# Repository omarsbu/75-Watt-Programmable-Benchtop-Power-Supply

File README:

In progress...
  => Finish Fusion 360 schematic & PCB layout
  => Finish Microcontroller Software

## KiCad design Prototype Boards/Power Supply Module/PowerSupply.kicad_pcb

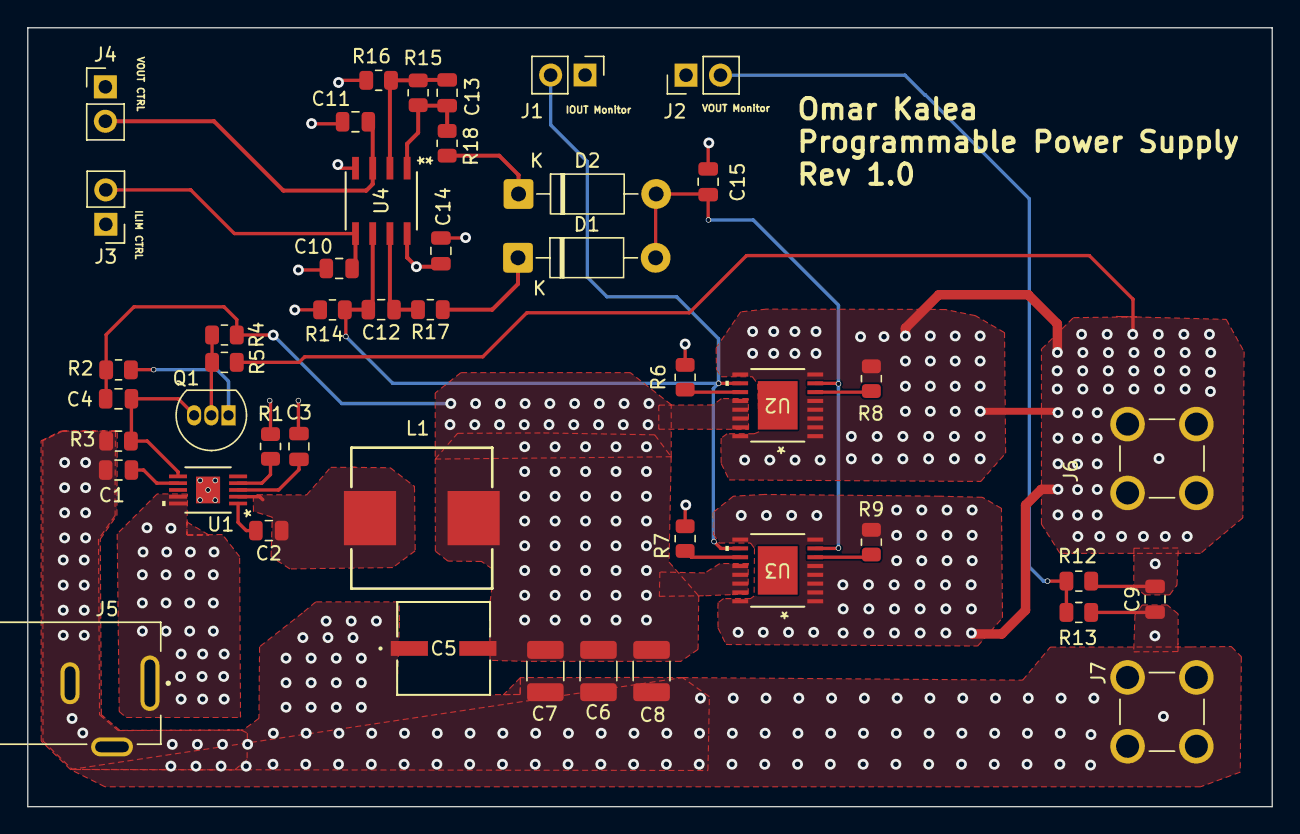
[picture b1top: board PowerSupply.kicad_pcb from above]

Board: 4 copper layers, 91.9 x 57.5 mm, 46 parts (0 on the bottom side), 26 nets.

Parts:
C1, C2, C10, C11, C14, C15: 0.1u; C_0805_2012Metric
C3: 1u; C_0805_2012Metric
C4, C12: 1n; C_0805_2012Metric
C5: 100u; CHEMI-F80-L
C6, C7, C8: 33u; C_1210_3225Metric_Pad1.33x2.70mm_HandSolder
C9: 10u; C_0805_2012Metric
C13: 100p; C_0805_2012Metric
D1, D2: 1N5819; D_DO-41_SOD81_P10.16mm_Horizontal
J1, J2, J3, J4: PinHeader_1x02_P2.54mm_Vertical
J5: 54-00130; TENSILITY_54-00130
J6: CT3151-2; CALTEST_CT3151-0
J7: CT3151-0; CALTEST_CT3151-0
L1: 2.2uH; WE-HCI_1050
Q1: 2N3906; TO-92_Inline
R1: 20k; R_0805_2012Metric
R2, R6, R7, R13, R16: 1k; R_0805_2012Metric
R3: 4k; R_0805_2012Metric
R4, R5: 100k; R_0805_2012Metric
R8, R9: 10k; R_0805_2012Metric
R12, R15: 9k; R_0805_2012Metric
R14: 5k; R_0805_2012Metric
R17, R18: 10; R_0805_2012Metric
U1: LT8609HMSE-TRPBF; 05-08-1664_ADI
U2, U3: LT3081HFE-PBF; TSSOP-16_FE&slash_BB_LIT-L
U4: ADA4091-2ARZ-R7; R_8_ADI-L

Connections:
+24V: C14.2, J5.A, U1.9 (VIN), U1.10 (EN/UV), U4.8 (V+)
/Power Stage/IMON: C12.2, J1.2, R14.1, U2.10 (IMON), U3.10 (IMON), U4.6 (INB-)
/Power Stage/LDO_IN: C4.1, C5.2, C6.2, C7.2, C8.2, L1.2, R2.2, R4.1, U2.12 (IN), U2.13 (IN), U2.14 (IN), U2.15 (IN), U3.12 (IN), U3.13 (IN), U3.14 (IN), U3.15 (IN)
/Power Stage/SW: C2.1, L1.1, U1.2 (SW)
/Power Stage/VMON: J2.2, R12.1, R13.2
/Power Stage/VSET: C15.1, D1.2 (A), D2.2 (A), U2.7 (SET), U3.7 (SET)
/Setpoint Control/CC_SET: C10.1, J3.2, U4.5 (INB+)
/Setpoint Control/CV_SET: C11.1, J4.2, U4.3 (INA+)
GND: C1.2, C3.1, C5.1, C6.1, C7.1, C8.1, C9.1, C10.2, C11.2, C14.1, C15.2, J1.1, J2.1, J3.1, J4.1, J5.B, J5.C, J7.1, J7.2 (1), J7.3 (1), J7.4 (1), R1.1, R3.1, R6.1, R7.1, R13.1, R14.2, R16.2, U1.11 (GND), U2.17 (EPAD), U3.17 (EPAD), U4.4 (V-)
unnamed: D1.1 (K), R17.1
unnamed: D2.1 (K), R18.1
unnamed: Q1.2 (B), R4.2, R5.1
unnamed: C4.2, Q1.3 (C), R3.2, U1.6 (FB)
unnamed: Q1.1 (E), R2.1
unnamed: C2.2, U1.1 (BST)
unnamed: C3.2, U1.3 (INTVCC)
unnamed: R1.2, U1.4 (RT)
unnamed: C1.1, U1.7 (TR/SS)
unnamed: R8.2, U2.6 (ILIM)
unnamed: R6.2, U2.11 (TEMP)
unnamed: R9.1, U3.6 (ILIM)
unnamed: R7.2, U3.11 (TEMP)
unnamed: C13.2, R15.2, R16.1, U4.2 (INA-)
unnamed: C13.1, R15.1, R18.2, U4.1 (OUTA)
unnamed: C12.1, R17.2, U4.7 (OUTB)
VOUT: C9.2, J6.1, J6.2 (1), J6.3 (1), J6.4 (1), R5.2, R8.1, R9.2, R12.2, U2.1 (OUT), U2.2 (OUT), U2.3 (OUT), U2.4 (OUT), U2.5 (OUT), U2.8 (OUT), U2.9 (OUT), U2.16 (OUT), U3.1 (OUT), U3.2 (OUT), U3.3 (OUT), U3.4 (OUT), U3.5 (OUT), U3.8 (OUT), U3.9 (OUT), U3.16 (OUT)

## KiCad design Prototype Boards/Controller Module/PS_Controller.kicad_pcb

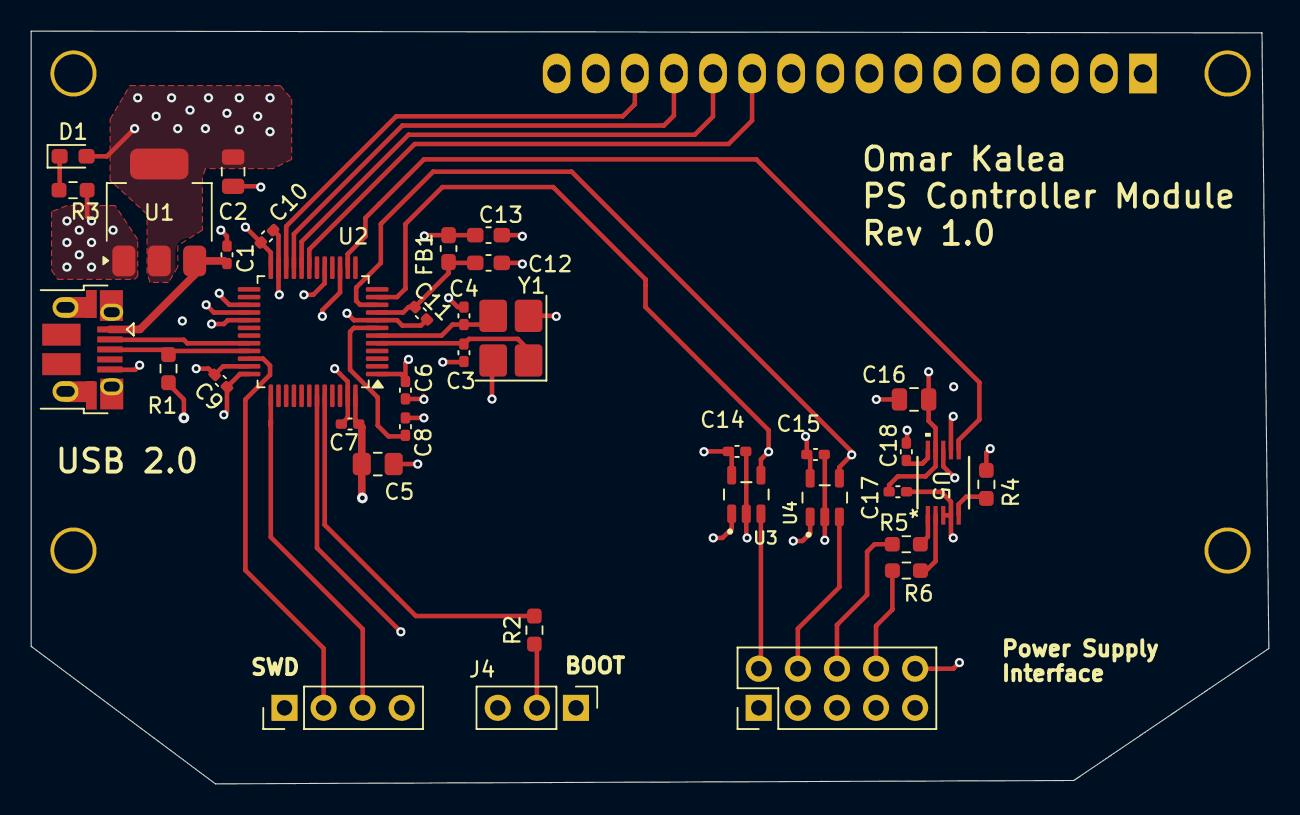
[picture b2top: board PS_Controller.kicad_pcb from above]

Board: 4 copper layers, 80.4 x 48.9 mm, 37 parts (1 on the bottom side), 35 nets.

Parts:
C1, C6, C7, C8, C9, C10, C11, C14, C15, C17, C18: 0.1u; C_0402_1005Metric_Pad0.74x0.62mm_HandSolder
C2, C16: 10u; C_0805_2012Metric
C3, C4: 10p; C_0402_1005Metric_Pad0.74x0.62mm_HandSolder
C5: 10u; C_0805_2012Metric_Pad1.18x1.45mm_HandSolder
C12, C13: 1u; C_0603_1608Metric_Pad1.08x0.95mm_HandSolder
D1: RED; LED_0603_1608Metric_Pad1.05x0.95mm_HandSolder
DS1: WC1602A
FB1: 120R; L_0603_1608Metric_Pad1.05x0.95mm_HandSolder
J1: Conn_02x05_Odd_Even; PinHeader_2x05_P2.54mm_Vertical
J2: Conn_01x04; PinHeader_1x04_P2.54mm_Vertical
J3: USB_B_Micro; USB_Micro-B_Amphenol_10103594-0001LF_Horizontal
J4: Conn_01x03; PinHeader_1x03_P2.54mm_Vertical
R1, R3: 1.5k; R_0603_1608Metric_Pad0.98x0.95mm_HandSolder
R2, R4: 10k; R_0603_1608Metric_Pad0.98x0.95mm_HandSolder
R5, R6: 50; R_0603_1608Metric_Pad0.98x0.95mm_HandSolder
U1: LD1117S33TR_SOT223; SOT-223-3_TabPin2
U2: STM32F103C8T6; LQFP-48_7x7mm_P0.5mm
U3, U4: OPA388IDBVR; SOT95P280X145-5N
U5: AD5623RBRMZ-5; AD5623RBRMZ_5
Y1: 16MHz; Crystal_SMD_3225-4Pin_3.2x2.5mm_HandSoldering

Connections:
+3.3V: C2.2, C5.2, C6.2, C7.2, C9.2, C10.2, C13.2, C14.2, C15.2, C16.2, C17.1, D1.2 (A), DS1.2 (VDD), DS1.15 (LED(+)), FB1.2, J2.1, J4.1, R1.1, R4.2, U1.2 (VO), U2.1 (VBAT), U2.24 (VDD), U2.36 (VDD), U2.48 (VDD), U3.5, U4.5, U5.9 (VDD)
+3.3VA: C11.2, C12.2, FB1.1, U2.9 (VDDA)
+VUSB: C1.2, J3.1 (VBUS), U1.3 (VI)
/Analog Interface/ADC_IN_0: U2.10 (PA0), U4.1, U4.4 (-)
/Analog Interface/ADC_IN_1: U2.11 (PA1), U3.1, U3.4 (-)
/Analog Interface/CC_SET: J1.8, R6.1
/Analog Interface/CV_SET: J1.6, R5.1
/Analog Interface/DAC_DIN: U2.17 (PA7), U5.8 (DIN)
/Analog Interface/DAC_SCLK: U2.15 (PA5), U5.7 (SCLK)
/Analog Interface/DAC_SYNC: U2.14 (PA4), U5.6 (*SYNC)
/Analog Interface/IMON: J1.4, U4.3 (+)
/Analog Interface/VMON: J1.2, U3.3 (+)
/Analog Interface/VOUTA: R5.2, U5.1 (VOUTA)
/Analog Interface/VOUTB: R6.2, U5.2 (VOUTB)
/LCD_D0: DS1.14 (D7), U2.22 (PB11)
/LCD_D1: DS1.13 (D6), U2.21 (PB10)
/LCD_D2: DS1.12 (D5), U2.20 (PB2)
/LCD_D3: DS1.11 (D4), U2.19 (PB1)
/LCD_E: DS1.6 (E), U2.27 (PB14)
/LCD_RS: DS1.4 (RS), U2.29 (PA8)
/LCD_RW: DS1.5 (R/W), U2.28 (PB15)
/Microcontroller/BOOT0: R2.2, U2.44 (BOOT0)
/Microcontroller/BOOT0_SEL: J4.2, R2.1
/Microcontroller/HSE_IN: C3.2, U2.5 (PD0), Y1.1
/Microcontroller/HSE_OUT: C4.2, U2.6 (PD1), Y1.3
/Microcontroller/NRST: C8.2, U2.7 (NRST)
/Microcontroller/PS_EN: J1.10, U2.43 (PB7)
/Microcontroller/SWCLK: J2.3, U2.37 (PA14)
/Microcontroller/SWDIO: J2.2, U2.34 (PA13)
/Microcontroller/USB_D+: J3.3 (D+), R1.2, U2.33 (PA12)
/Microcontroller/USB_D-: J3.2 (D-), U2.32 (PA11)
GND: C1.1, C2.1, C3.1, C4.1, C5.1, C6.1, C7.1, C8.1, C9.1, C10.1, C11.1, C12.1, C13.1, C14.1, C15.1, C16.1, C17.2, C18.1, DS1.1 (VSS), DS1.3 (VO), DS1.16 (LED(-)), J1.1, J1.3, J1.5, J1.7, J1.9, J2.4, J3.5 (GND), J4.3, R3.2, U1.1 (GND), U2.8 (VSSA), U2.23 (VSS), U2.35 (VSS), U2.47 (VSS), U3.2, U4.2, U5.3 (GND), U5.4 (*LDAC), Y1.2, Y1.4
unnamed: D1.1 (K), R3.1
unnamed: R4.1, U5.5 (*CLR)
unnamed: C18.2, U5.10 (VREFIN/VREFOUT)

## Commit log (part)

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2024-08-30 Rename README to README.md
2025-12-07 Rename Programmable_power_supply_protection.asc to LTspice/Programmable_power_supply_protection.asc
2025-12-07 Rename CURRENT_LIMITING.asc to LTspice/CURRENT_LIMITING.asc
